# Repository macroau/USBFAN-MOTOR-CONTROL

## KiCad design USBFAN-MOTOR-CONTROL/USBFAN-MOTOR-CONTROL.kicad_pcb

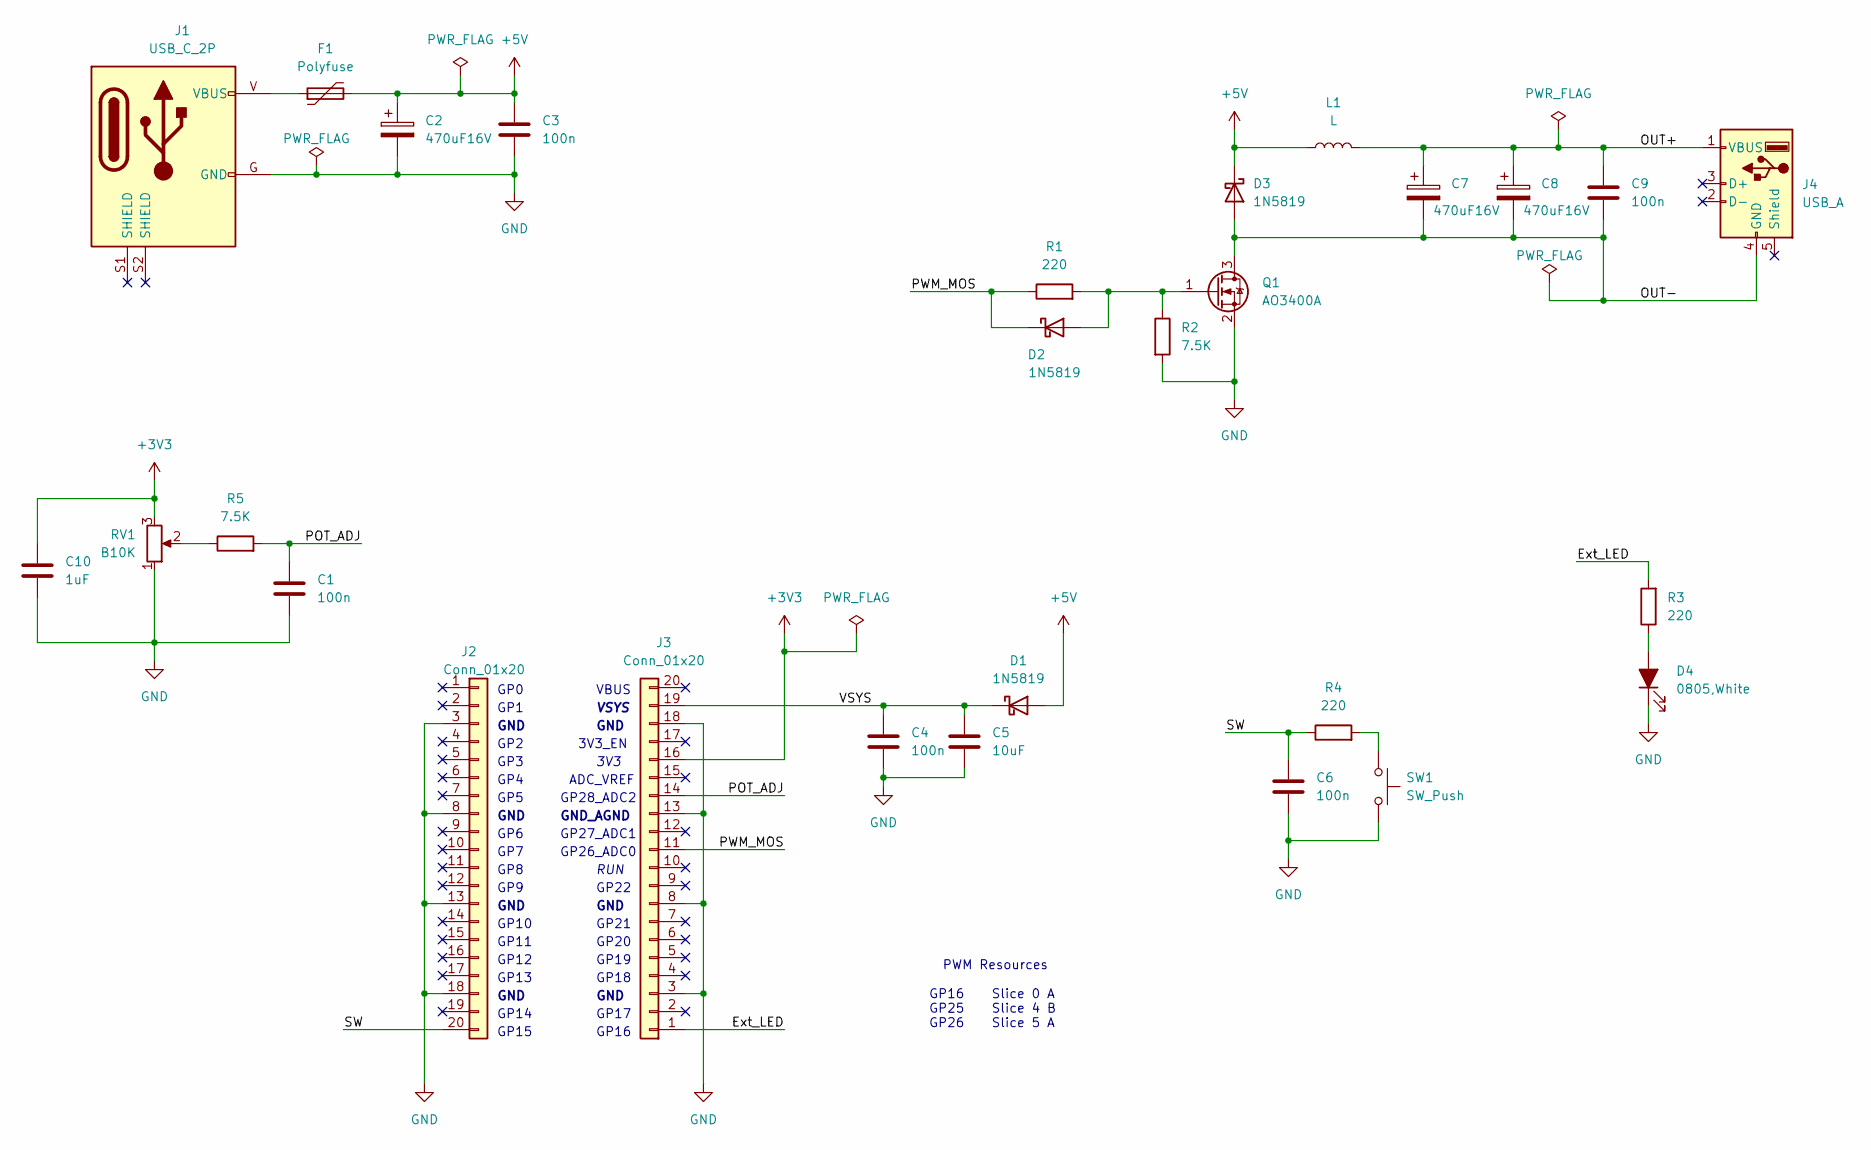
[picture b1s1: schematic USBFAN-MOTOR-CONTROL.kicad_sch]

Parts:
C1, C3, C4, C6, C9: 100n; C_0603_1608Metric_Pad1.08x0.95mm_HandSolder
C2, C7, C8: 470uF16V; CP_Radial_D8.0mm_P3.50mm
C5: 10uF; C_0805_2012Metric_Pad1.18x1.45mm_HandSolder
C10: 1uF; C_0805_2012Metric_Pad1.18x1.45mm_HandSolder
D1, D2, D3: 1N5819; D_SOD-323_HandSoldering
D4: 0805,White; LED_0805_2012Metric_Pad1.15x1.40mm_HandSolder
F1: Polyfuse; Fuse_0805_2012Metric_Pad1.15x1.40mm_HandSolder
J1: USB_C_2P; USB_TYPE_C_2P_THT_90
J2, J3: Conn_01x20; PinSocket_1x20_P2.54mm_Vertical
J4: USB_A; USB_A_CONNFLY_DS1095-WNR0
L1: L; L_Radial_D10.0mm_P5.00mm_Fastron_07M
Q1: AO3400A; SOT-23
R1, R3, R4: 220; R_0603_1608Metric_Pad0.98x0.95mm_HandSolder
R2, R5: 7.5K; R_0603_1608Metric_Pad0.98x0.95mm_HandSolder
RV1: B10K; POT_SINGLE_WH148
SW1: SW_Push; SW_PUSH_6mm_H7.3mm

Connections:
+3V3: C10.1, J3.16, RV1.3
+5V: C2.1, C3.1, D1.2 (A), D3.1 (K), F1.2, L1.1
/Ext_LED: J3.1, R3.2
/OUT+: C7.1, C8.1, C9.1, J4.1 (VBUS), L1.2
/OUT-: C7.2, C8.2, C9.2, D3.2 (A), J4.4 (GND), Q1.3 (D)
/POT_ADJ: C1.1, J3.14, R5.2
/PWM_MOS: D2.1 (K), J3.11, R1.1
/SW: C6.1, J2.20, R4.1
/VSYS: C4.1, C5.1, D1.1 (K), J3.19
GND: C1.2, C2.2, C3.2, C4.2, C5.2, C6.2, C10.2, D4.1 (K), J1.G (GND), J2.3, J2.8, J2.13, J2.18, J3.3, J3.8, J3.13, J3.18, Q1.2 (S), R2.2, RV1.1, SW1.2
unnamed: D2.2 (A), Q1.1 (G), R1.2, R2.1
unnamed: D4.2 (A), R3.1
unnamed: F1.1, J1.V (VBUS)
unnamed: R5.1, RV1.2
unnamed: R4.2, SW1.1

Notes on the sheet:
GP0
GP1
GND
GP2
GP3
GP4
GP5
GP6
GP7
GP8
GP9
GP10
GP11
GP12
GP13
GP14
GP15
GP28_ADC2
GND_AGND
GP27_ADC1
GP26_ADC0
ADC_VREF
3V3_EN
VBUS
VSYS
3V3
RUN
GP22
GP21
GP20
GP19
GP18
GP17
GP16
PWM Resources GP16 Slice 0 A GP25 Slice 4 B GP26 Slice 5 A

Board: 2 copper layers, 28 parts (20 on the bottom side), 15 nets, no tracks yet.

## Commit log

2021-08-21 modified: .gitignore new file: USBFAN-MOTOR-CONTROL/USBFAN-MOTOR-CONTROL.kicad_pcb new file: USBFAN-MOTOR-CONTROL/USBFAN-MOTOR-CONTROL.kicad_prl new file: USBFAN-MOTOR-CONTROL/USBFAN-MOTOR-CONTROL.ki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
2021-08-21 MicroPython code added
    Changes to be committed:
    new file: micropython/main.py
2021-08-23 schematics finalized and pcb generated.
    Changes to be committed:
    modified: USBFAN-MOTOR-CONTROL/USBFAN-MOTOR-CONTROL.kicad_pcb
    modified: USBFAN-MOTOR-CONTROL/USBFAN-MOTOR-CONTROL.kicad_prl
    modified: USBFAN-MOTOR-CONTROL/USBFAN-MOTOR-CONTROL.kicad_sch
    new file: USBFAN-MOTOR-CONTROL/fp-info-cache
